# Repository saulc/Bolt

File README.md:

# Bolt

Hackaday.io prize 2023 Round 1 Re-engineering Education Finalist.<br>
https://hackaday.io/project/190291-bolt-bots-micro-servo-droids
<br>
Lesson 0 - Teach the teachers how to use github.<br>

 Bolt Botz - Robotics Curriculum Options<br>
 Open Source Hardware, Software and Curriculum!<br>

 Presentation - Show students what Exists Now.<br>
 Build and Interact - Hands on demo are always more engaging and interesting<br>
 Programming - Build on a library(if I write one) or Write Full control code yourself<br>
 Control Circuits - Built a bespoke circuit with an Arduino starter kit or hand soldered project board<br>
 Custom parts and code - Create combine parts and add features.<br>
 Build with Boltz - build something new with a few bolt bits...<br>

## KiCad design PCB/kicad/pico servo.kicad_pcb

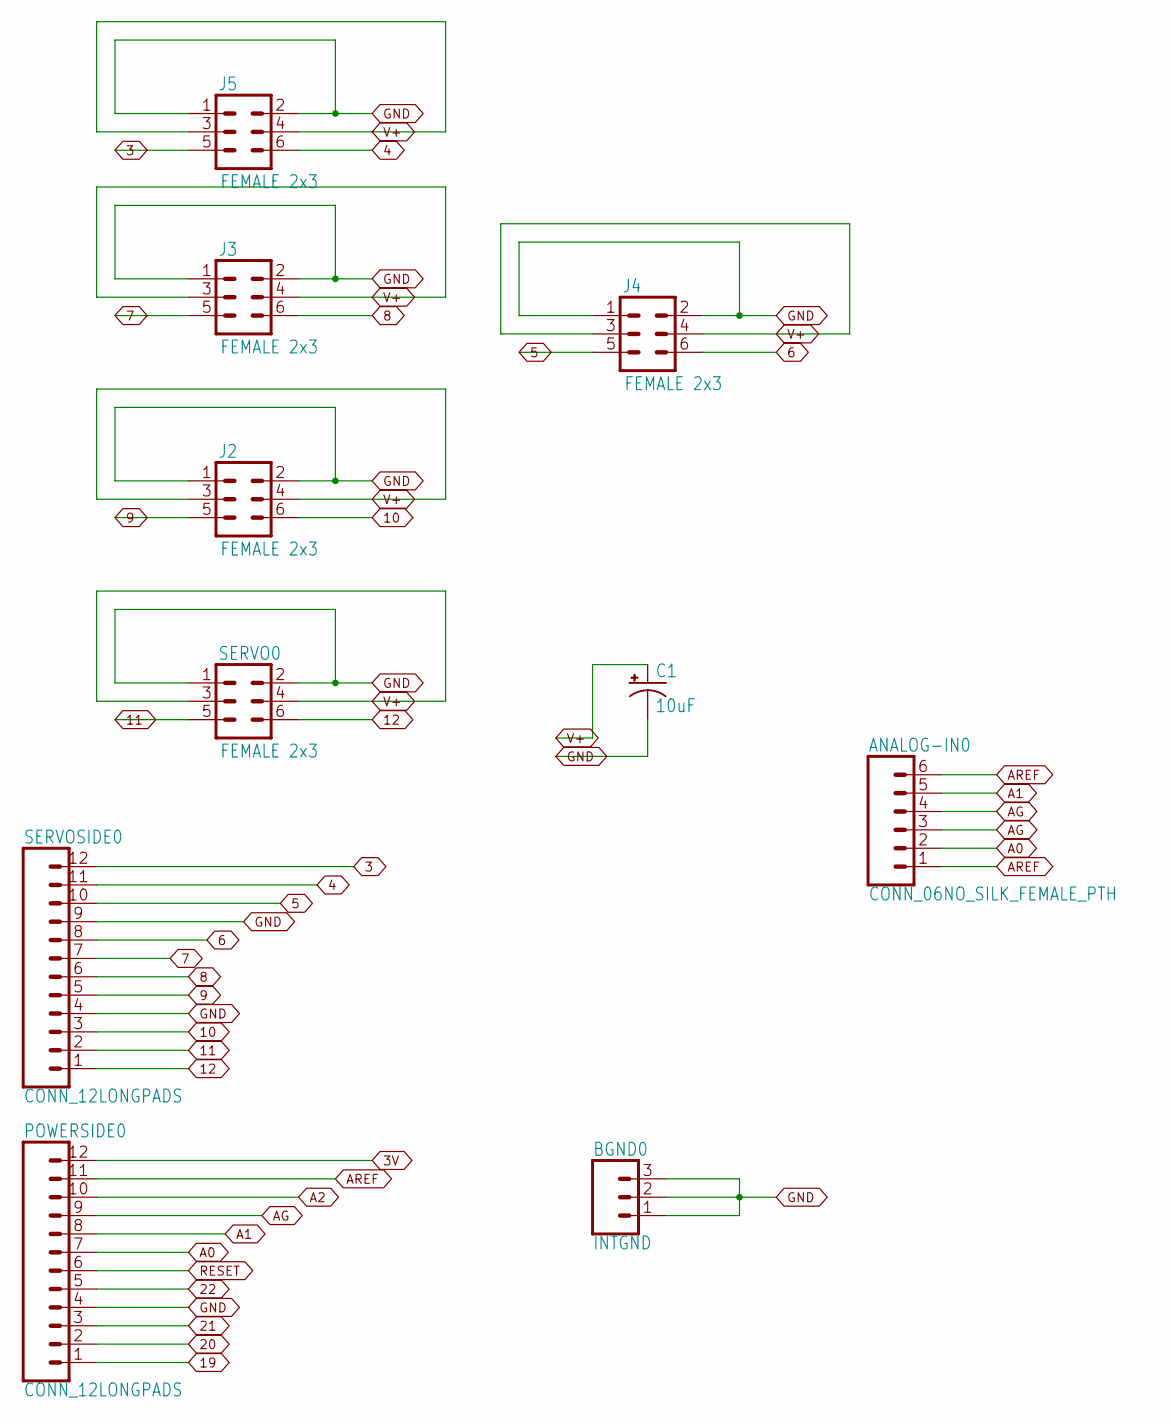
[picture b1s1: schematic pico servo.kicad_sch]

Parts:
ANALOG-IN0: CONN_06NO_SILK_FEMALE_PTH; 1X06_NO_SILK
BGND0: INTGND; 1X03
C1: 10uF; CPOL-RADIAL-2.5MM-5MM
J2, J3, J4, J5: FEMALE 2x3; 2X3
POWERSIDE0: CONN_12LONGPADS; 1X12_LONGPADS
SERVO0: FEMALE 2x3; 2X3
SERVOSIDE0: CONN_12LONGPADS; 1X12_LONGPADS

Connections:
3: J5.5, SERVOSIDE0.12
3V: POWERSIDE0.12
4: J5.6, SERVOSIDE0.11
5: J4.5, SERVOSIDE0.10
6: J4.6, SERVOSIDE0.8
7: J3.5, SERVOSIDE0.7
8: J3.6, SERVOSIDE0.6
9: J2.5, SERVOSIDE0.5
10: J2.6, SERVOSIDE0.3
11: SERVO0.5, SERVOSIDE0.2
12: SERVO0.6, SERVOSIDE0.1
19: POWERSIDE0.1
20: POWERSIDE0.2
21: POWERSIDE0.3
22: POWERSIDE0.5
A0: ANALOG-IN0.2, POWERSIDE0.7
A1: ANALOG-IN0.5, POWERSIDE0.8
A2: POWERSIDE0.10
AG: ANALOG-IN0.3, ANALOG-IN0.4, POWERSIDE0.9
AREF: ANALOG-IN0.1, ANALOG-IN0.6, POWERSIDE0.11
GND: BGND0.1, BGND0.2, BGND0.3, C1.2 (-), J2.1, J2.2, J3.1, J3.2, J4.1, J4.2, J5.1, J5.2, POWERSIDE0.4, SERVO0.1, SERVO0.2, SERVOSIDE0.4, SERVOSIDE0.9
RESET: POWERSIDE0.6
V+: C1.1 (+), J2.3, J2.4, J3.3, J3.4, J4.3, J4.4, J5.3, J5.4, SERVO0.3, SERVO0.4

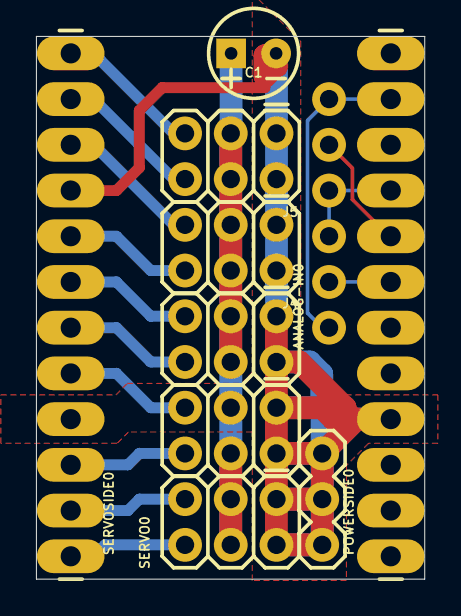
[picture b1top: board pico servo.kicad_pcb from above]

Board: 2 copper layers, 21.6 x 30.1 mm, 10 parts (0 on the bottom side), 16 nets.

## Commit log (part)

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2023-04-22 design files
    ...
2023-04-26 Tone Wheel Test
    servo interferance...
2023-04-26 scorpion
    code name banchii
2023-04-28 tone test
    small update.. speed is good!
2023-05-01 curved ducts
    ...
2023-05-02 toroidal propeller
    kinda...v1
2023-05-02 tor
    donuts, still no thrust..
2023-05-03 drawbot test on pico
    more speed = less skips?
2023-05-11 drawbot
    stepservo class
2023-05-13 bubbles
    and readme update.
2023-05-13 ..
    read me formatting?
2023-05-13 readme
    format..
2023-05-13 Pico servo board
    ...nrf servo board base
2023-05-13 needs labels
    extend to vsys(vin?)
2023-05-15 rz
    no more car for now...
2023-07-07 box bot
    ....
